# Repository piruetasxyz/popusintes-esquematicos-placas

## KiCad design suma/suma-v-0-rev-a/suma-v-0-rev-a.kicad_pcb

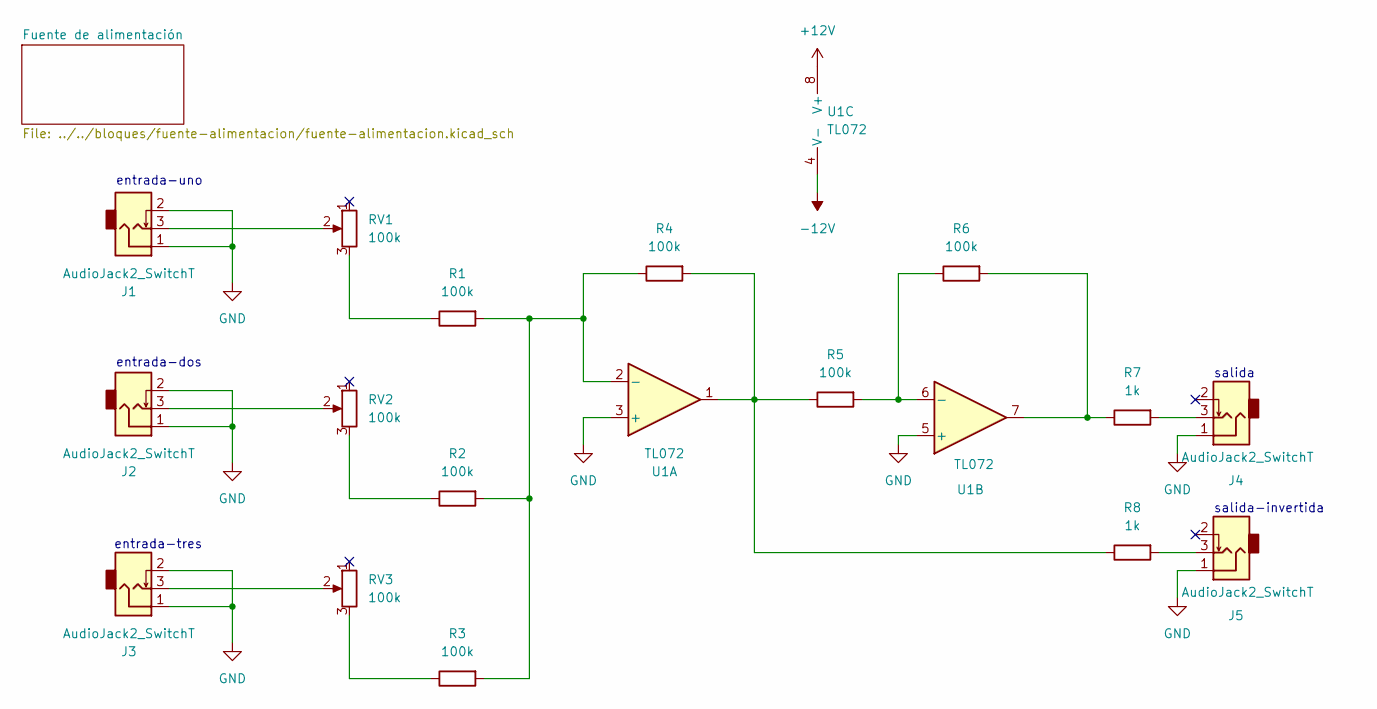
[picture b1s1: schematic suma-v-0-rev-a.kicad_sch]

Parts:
J1, J2, J3, J4, J5: AudioJack2_SwitchT; Jack_3.5mm_QingPu_WQP-PJ398SM_Vertical
R1, R2, R3, R4, R5, R6: 100k; R0805
R7, R8: 1k; R0805
RV1, RV2, RV3: 100k; POT_TH_Alps_RK09K_Single_Vertical
U1: TL072; SOIC-8_L4.9-W3.9-P1.27-LS6.0-BL

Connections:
+12V: U1.8 (V+); also elsewhere on the board
-12V: U1.4 (V-); also elsewhere on the board
GND: J1.1, J1.2, J2.1, J2.2, J3.1, J3.2, J4.1, J5.1, U1.3 (+), U1.5 (+); also elsewhere on the board
unnamed: J1.3, RV1.2
unnamed: J2.3, RV2.2
unnamed: J3.3, RV3.2
unnamed: J4.3, R7.2
unnamed: J5.3, R8.2
unnamed: R1.1, RV1.3
unnamed: R2.1, RV2.3
unnamed: R3.1, RV3.3
unnamed: R4.2, R5.1, R8.1, U1.1
unnamed: R6.2, R7.1, U1.7
unnamed: R1.2, R2.2, R3.2, R4.1, U1.2 (-)
unnamed: R5.2, R6.1, U1.6 (-)

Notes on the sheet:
salida-invertida
entrada-tres
entrada-uno
salida
entrada-dos

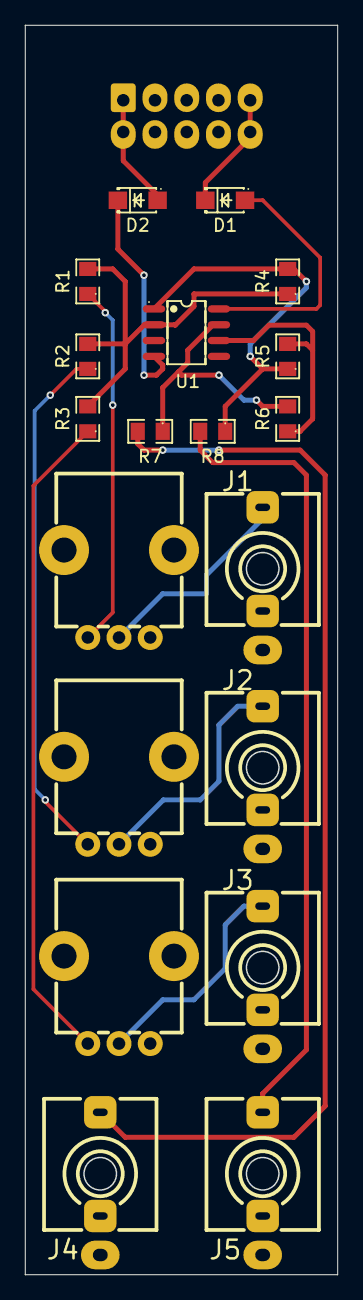
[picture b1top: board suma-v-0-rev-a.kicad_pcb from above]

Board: 2 copper layers, 25.0 x 100.0 mm, 20 parts (1 on the bottom side), 17 nets.

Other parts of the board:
D1, D2: D_Schottky; SOD-123FL_L2.8-W1.8-LS3.7-R-RD
J6: Conn_02x05_Odd_Even; IDC-Header_2x05_P2.54mm_Vertical

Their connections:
+12V: D1.1 (K); also elsewhere on the board
-12V: D2.2 (A); also elsewhere on the board
GND: J6.3, J6.4, J6.5, J6.6, J6.7, J6.8; also elsewhere on the board
unnamed: D1.2 (A), J6.9, J6.10
unnamed: D2.1 (K), J6.1, J6.2
